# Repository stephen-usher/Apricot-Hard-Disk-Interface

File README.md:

# Apricot-Hard-Disk-Interface
 This is a board for the ACT Apricot series of computers providing virtual hard disks held on a FAT format microSD card.

 The core of this is a Raspberry Pi Pico which pretends to be most of the circuity on the original "Winchester Card", i.e. the WD1010-05 MFM hard disk controller chip, the 8K transfer static RAM and the  control latch. The main address translation is done via the two GALs and data/addresses and voltage levels are managed via the 74LS and 74AHCT chips controlled by the GALs.

 The board can be built in two forms. The first is fully populated and is a stand-alone unit which just plugs into the Apricot expansion bus connector. The second form is as a daughter board to my RAM  expansion card (which needs one bodge wire added to bring the ALE signal to the expansion connector) in which case it only requires the two 74AHCT chips and one GAL as all the other functionality is  provided by the RAM card.

 The source and binaries for the GAL code can be found in the GAL sub-directory.

 The Raspberry Pi Pico's software is written in C using the Pico SDK. I used the version which runs on a Raspberry Pi 4 to develop this. One core is used for the host interface and the other for the less  time critical parts such as emulating the WD1010-05 commands and talking to the microSD card.

 The microSD card interface I used was easily found on Amazon and targetted at the Arduino, hence why it is a 5V model. It's an "AZ-Delivery SPI Reader Micro". Others will probably work but the pin-outs may  be different.

 The PCB was designed using KiCAD 6.

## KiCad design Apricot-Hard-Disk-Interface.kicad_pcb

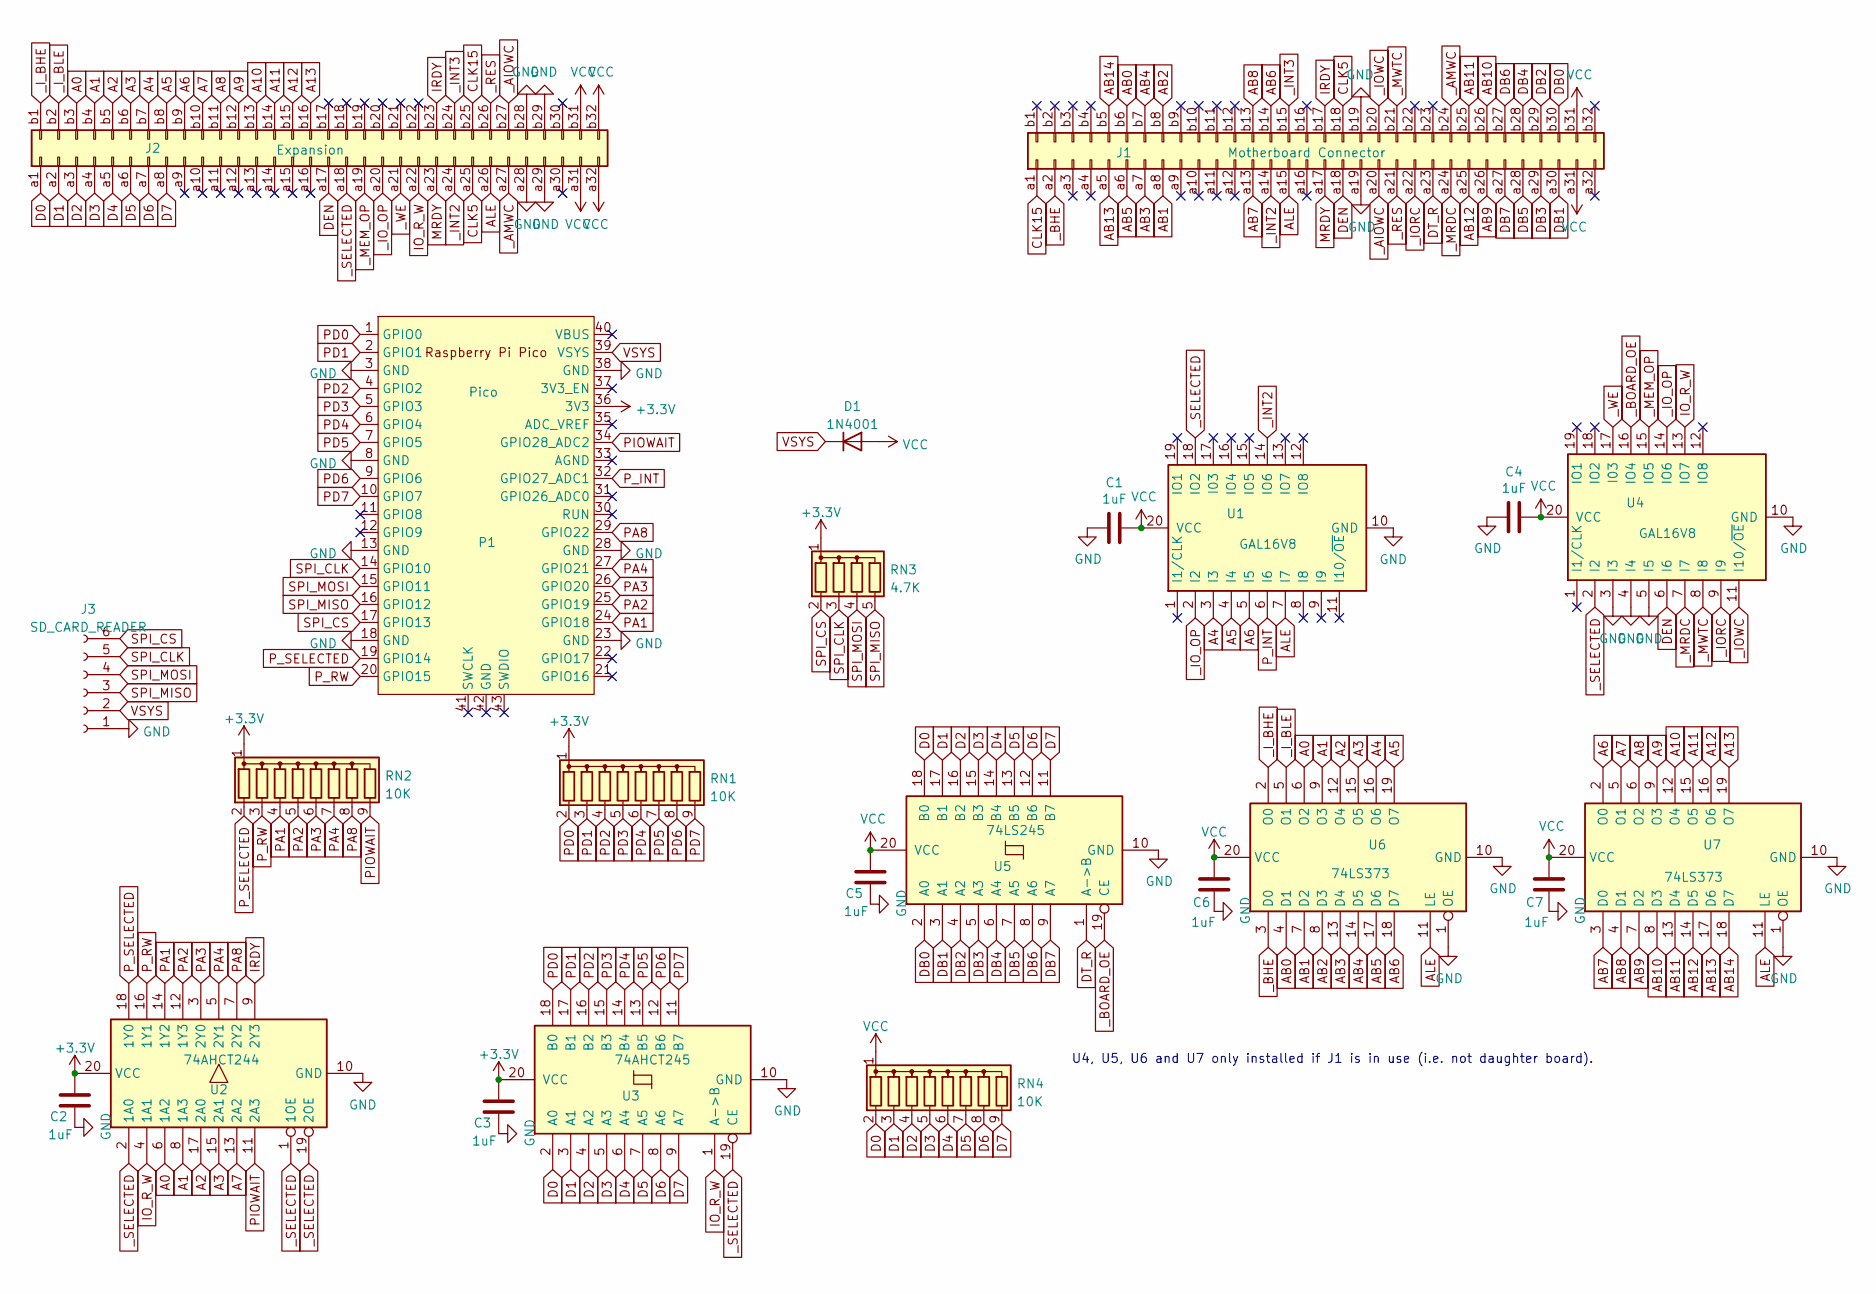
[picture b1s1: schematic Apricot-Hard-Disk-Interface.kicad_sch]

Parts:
C1, C2, C3, C4, C5, C6, C7: 1uF; C_0805_2012Metric
D1: 1N4001; D_DO-41_SOD81_P10.16mm_Horizontal
J1: Motherboard Connector; DIN41612_B_2x32_Male_Horizontal_THT
J2: Expansion; DIN41612_B_2x32_Female_Vertical_THT
J3: SD_CARD_READER; PinSocket_1x06_P2.54mm_Horizontal
P1: Pico; RPi_Pico_SMD_TH
RN1, RN2, RN4: 10K; R_Array_SIP9
RN3: 4.7K; R_Array_SIP5
U1, U4: GAL16V8; DIP-20_W7.62mm_Socket
U2: 74AHCT244; DIP-20_W7.62mm_Socket
U3: 74AHCT245; DIP-20_W7.62mm_Socket
U5: 74LS245; DIP-20_W7.62mm_Socket
U6, U7: 74LS373; DIP-20_W7.62mm_Socket

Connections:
+3.3V: C2.1, C3.1, P1.36 (3V3), RN1.1 (common), RN2.1 (common), RN3.1 (common), U2.20 (VCC), U3.20 (VCC)
A0: J2.b3, U2.6 (1A2), U6.6 (O2)
A1: J2.b4, U2.8 (1A3), U6.9 (O3)
A2: J2.b5, U2.17 (2A0), U6.12 (O4)
A3: J2.b6, U2.15 (2A1), U6.15 (O5)
A4: J2.b7, U1.3 (I3), U6.16 (O6)
A5: J2.b8, U1.4 (I4), U6.19 (O7)
A6: J2.b9, U1.5 (I5), U7.2 (O0)
A7: J2.b10, U2.13 (2A2), U7.5 (O1)
A8: J2.b11, U7.6 (O2)
A9: J2.b12, U7.9 (O3)
A10: J2.b13, U7.12 (O4)
A11: J2.b14, U7.15 (O5)
A12: J2.b15, U7.16 (O6)
A13: J2.b16, U7.19 (O7)
AB0: J1.b6, U6.4 (D1)
AB1: J1.a8, U6.7 (D2)
AB2: J1.b8, U6.8 (D3)
AB3: J1.a7, U6.13 (D4)
AB4: J1.b7, U6.14 (D5)
AB5: J1.a6, U6.17 (D6)
AB6: J1.b14, U6.18 (D7)
AB7: J1.a13, U7.3 (D0)
AB8: J1.b13, U7.4 (D1)
AB9: J1.a26, U7.7 (D2)
AB10: J1.b26, U7.8 (D3)
AB11: J1.b25, U7.13 (D4)
AB12: J1.a25, U7.14 (D5)
AB13: J1.a5, U7.17 (D6)
AB14: J1.b5, U7.18 (D7)
ALE: J1.a15, J2.a26, U1.7 (I7), U6.11 (LE), U7.11 (LE)
CLK5: J1.b18, J2.a25
CLK15: J1.a1, J2.b25
D0: J2.a1, RN4.2 (R1), U3.2 (A0), U5.18 (B0)
D1: J2.a2, RN4.3 (R2), U3.3 (A1), U5.17 (B1)
D2: J2.a3, RN4.4 (R3), U3.4 (A2), U5.16 (B2)
D3: J2.a4, RN4.5 (R4), U3.5 (A3), U5.15 (B3)
D4: J2.a5, RN4.6 (R5), U3.6 (A4), U5.14 (B4)
D5: J2.a6, RN4.7 (R6), U3.7 (A5), U5.13 (B5)
D6: J2.a7, RN4.8 (R7), U3.8 (A6), U5.12 (B6)
D7: J2.a8, RN4.9 (R8), U3.9 (A7), U5.11 (B7)
DB0: J1.b30, U5.2 (A0)
DB1: J1.a30, U5.3 (A1)
DB2: J1.b29, U5.4 (A2)
DB3: J1.a29, U5.5 (A3)
DB4: J1.b28, U5.6 (A4)
DB5: J1.a28, U5.7 (A5)
DB6: J1.b27, U5.8 (A6)
DB7: J1.a27, U5.9 (A7)
DEN: J1.a18, J2.a17, U4.6 (I6)
DT_R: J1.a23, U5.1 (A->B)
GND: C1.2, C2.2, C3.2, C4.2, C5.2, C6.2, C7.2, J1.a19, J1.b19, J2.a28, J2.a29, J2.b28, J2.b29, J3.1, P1.3 (GND), P1.8 (GND), P1.13 (GND), P1.18 (GND), P1.23 (GND), P1.28 (GND), P1.38 (GND), U1.10 (GND), U2.10 (GND), U3.10 (GND), U4.3 (I3), U4.4 (I4), U4.5 (I5), U4.10 (GND), U5.10 (GND), U6.1 (OE), U6.10 (GND), U7.1 (OE), U7.10 (GND)
IO_R_W: J2.a22, U2.4 (1A1), U3.1 (A->B), U4.13 (IO7)
IRDY: J1.b17, J2.b23, U2.9 (2Y3)
MRDY: J1.a17, J2.a23
PA1: P1.24 (GPIO18), RN2.4 (R3), U2.14 (1Y2)
PA2: P1.25 (GPIO19), RN2.5 (R4), U2.12 (1Y3)
PA3: P1.26 (GPIO20), RN2.6 (R5), U2.3 (2Y0)
PA4: P1.27 (GPIO21), RN2.7 (R6), U2.5 (2Y1)
PA8: P1.29 (GPIO22), RN2.8 (R7), U2.7 (2Y2)
PD0: P1.1 (GPIO0), RN1.2 (R1), U3.18 (B0)
PD1: P1.2 (GPIO1), RN1.3 (R2), U3.17 (B1)
PD2: P1.4 (GPIO2), RN1.4 (R3), U3.16 (B2)
PD3: P1.5 (GPIO3), RN1.5 (R4), U3.15 (B3)
PD4: P1.6 (GPIO4), RN1.6 (R5), U3.14 (B4)
PD5: P1.7 (GPIO5), RN1.7 (R6), U3.13 (B5)
PD6: P1.9 (GPIO6), RN1.8 (R7), U3.12 (B6)
PD7: P1.10 (GPIO7), RN1.9 (R8), U3.11 (B7)
PIOWAIT: P1.34 (GPIO28_ADC2), RN2.9 (R8), U2.11 (2A3)
P_INT: P1.32 (GPIO27_ADC1), U1.6 (I6)
P_RW: P1.20 (GPIO15), RN2.3 (R2), U2.16 (1Y1)
P_SELECTED: P1.19 (GPIO14), RN2.2 (R1), U2.18 (1Y0)
SPI_CLK: J3.5, P1.14 (GPIO10), RN3.3 (R2)
SPI_CS: J3.6, P1.17 (GPIO13), RN3.2 (R1)
SPI_MISO: J3.3, P1.16 (GPIO12), RN3.5 (R4)
SPI_MOSI: J3.4, P1.15 (GPIO11), RN3.4 (R3)
VCC: C1.1, C4.1, C5.1, C6.1, C7.1, D1.2 (A), J1.a31, J1.b31, J2.a31, J2.a32, J2.b31, J2.b32, RN4.1 (common), U1.20 (VCC), U4.20 (VCC), U5.20 (VCC), U6.20 (VCC), U7.20 (VCC)
VSYS: D1.1 (K), J3.2, P1.39 (VSYS)
_AIOWC: J1.a20, J2.b27
_AMWC: J1.b24, J2.a27
_BHE: J1.a2, U6.3 (D0)
_BOARD_OE: U4.16 (IO4), U5.19 (CE)
_INT2: J1.a14, J2.a24, U1.14 (IO6)
_INT3: J1.b15, J2.b24
_IORC: J1.a22, U4.9 (I9)
_IOWC: J1.b20, U4.11 (I10/~OE)
_IO_OP: J2.a20, U1.2 (I2), U4.14 (IO6)
_I_BHE: J2.b1, U6.2 (O0)
_I_BLE: J2.b2, U6.5 (O1)
_MEM_OP: J2.a19, U4.15 (IO5)
_MRDC: J1.a24, U4.7 (I7)
_MWTC: J1.b21, U4.8 (I8)
_RES: J1.a21, J2.b26
_SELECTED: J2.a18, U1.18 (IO2), U2.1 (1OE), U2.2 (1A0), U2.19 (2OE), U3.19 (CE), U4.2 (I2)
_WE: J2.a21, U4.17 (I03)

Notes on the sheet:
U4, U5, U6 and U7 only installed if J1 is in use (i.e. not daughter board).

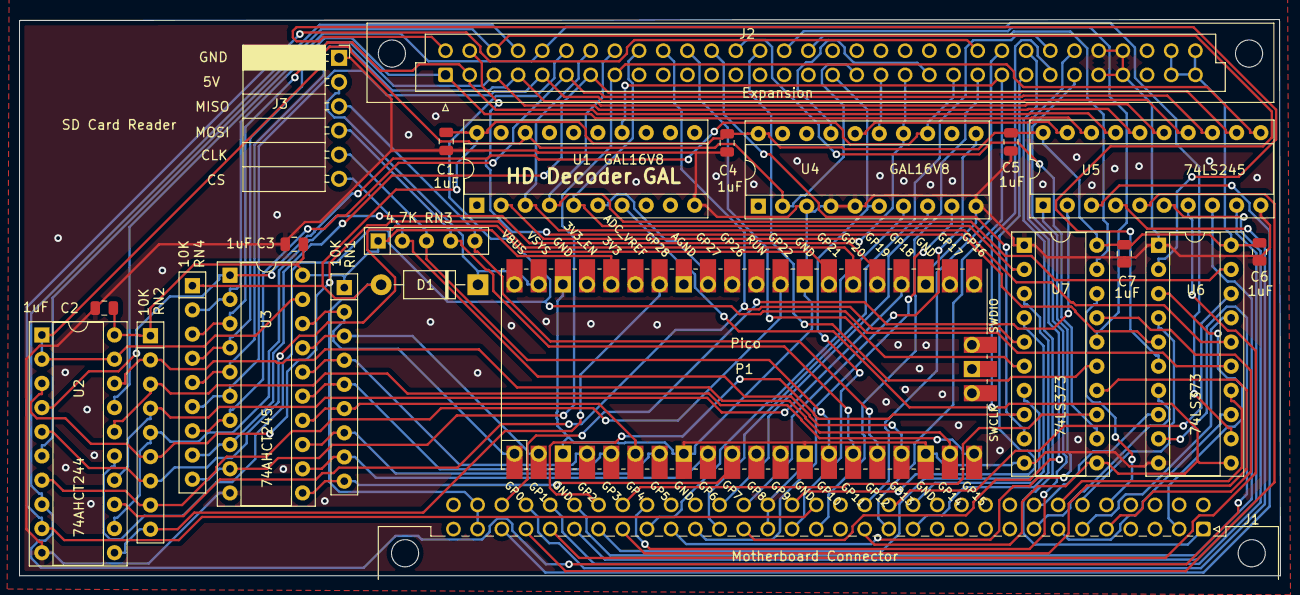
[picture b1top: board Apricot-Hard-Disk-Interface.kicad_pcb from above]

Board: 2 copper layers, 132.4 x 58.4 mm, 23 parts (0 on the bottom side), 95 nets.

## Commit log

2023-02-07 First import. Working system but Gerber files are for original design which needs bodging
2023-02-07 Updated the PCB to the latest schematic and routed the PCB. Added Readme.md files
2023-02-07 Deleted old and unused KiCAD schematic files from the false start of the project.
2023-02-08 Updated the Pico source Readme.md file.
2023-02-22 Added documentation & new HD images
2023-03-26 Replaced/Added separate hard disk images for F Series and Portable

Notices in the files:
Apricot-Hard-Disk-Interface.kicad_pcb:
© Stephen Usher 2023
